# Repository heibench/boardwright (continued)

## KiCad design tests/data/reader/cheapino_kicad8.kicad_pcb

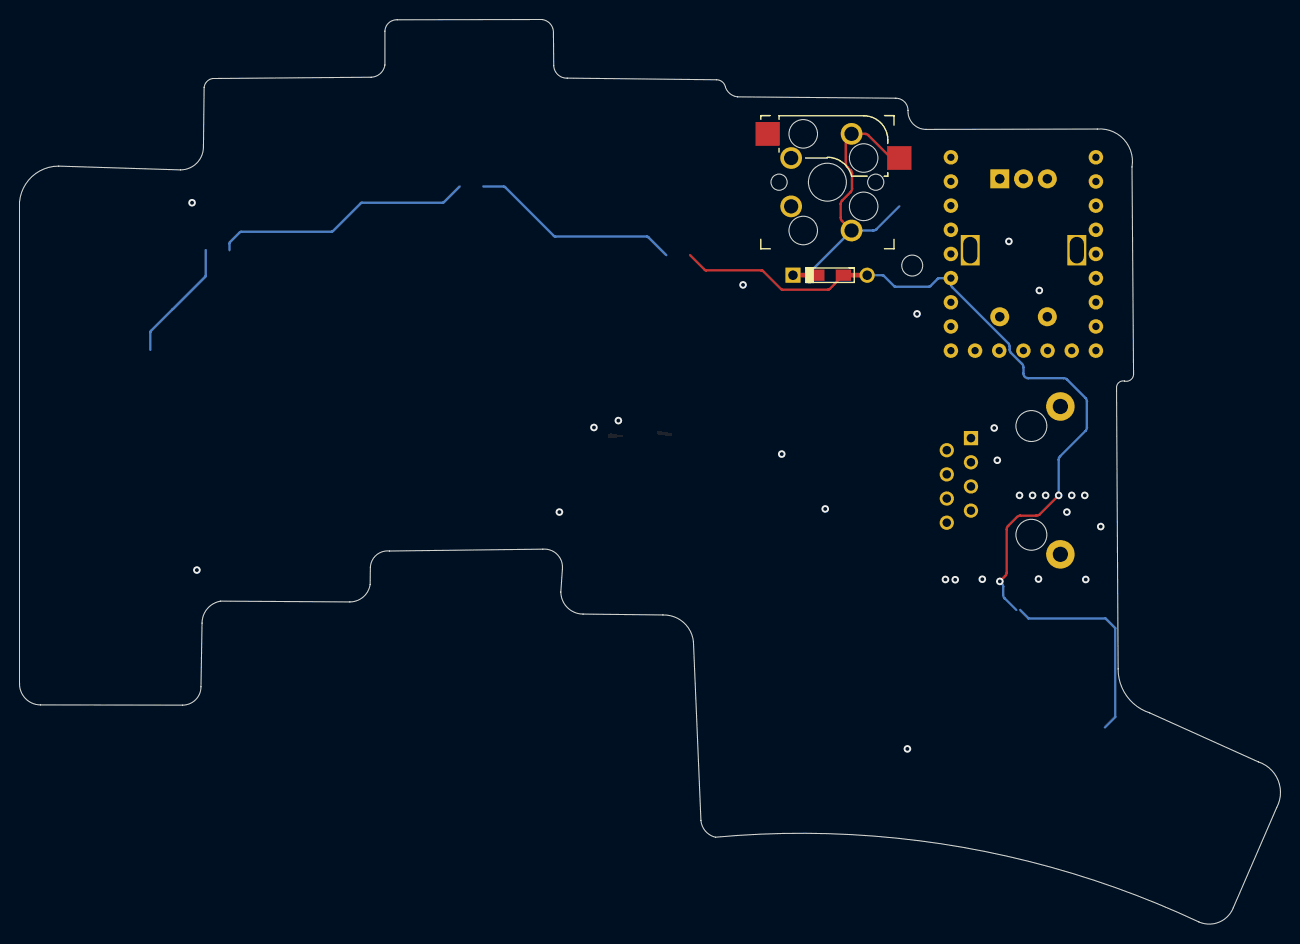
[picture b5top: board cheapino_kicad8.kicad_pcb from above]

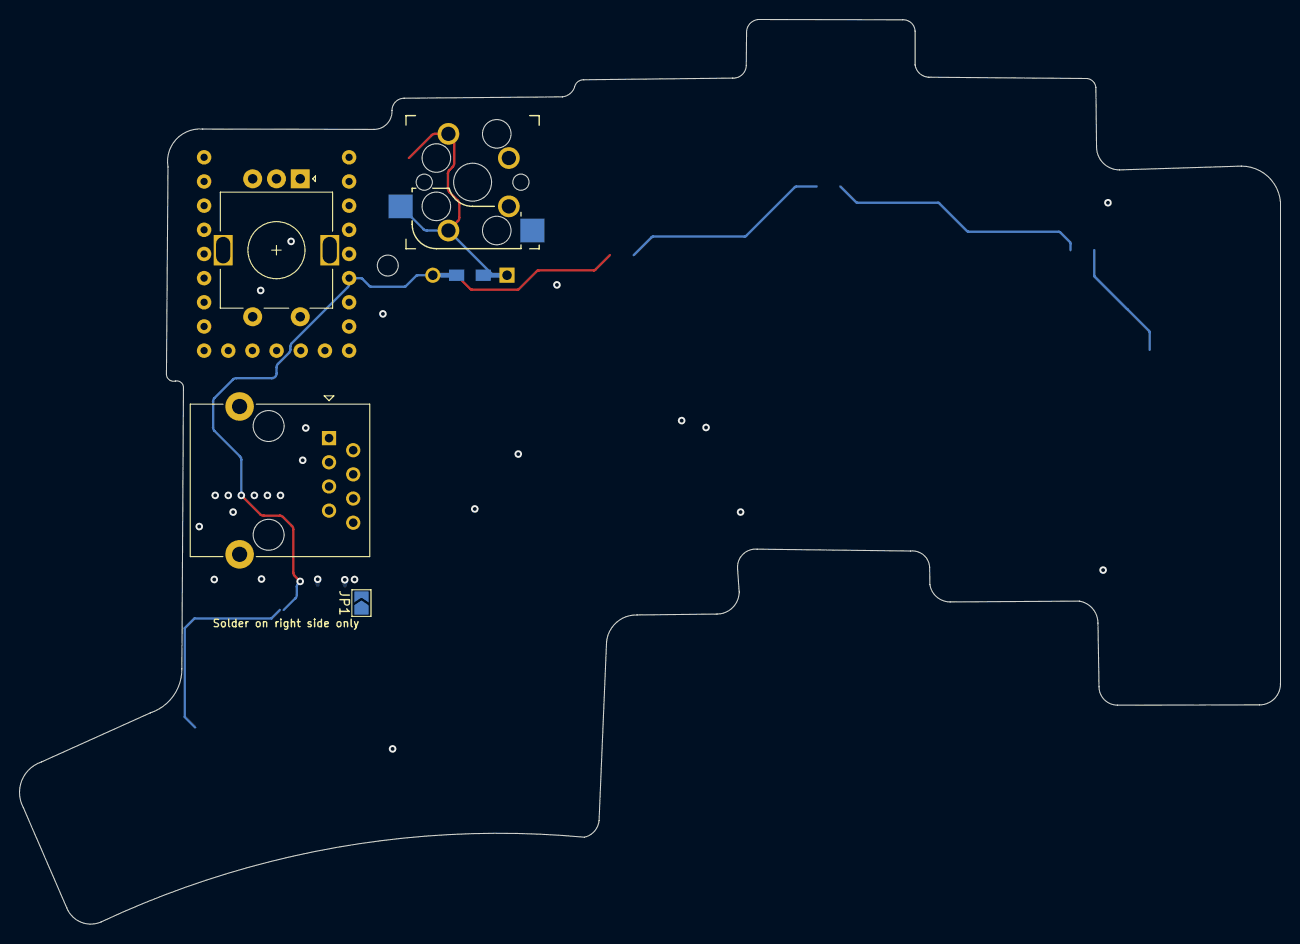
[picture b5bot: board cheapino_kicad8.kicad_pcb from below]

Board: 2 copper layers, 132.5 x 95.1 mm, 6 parts (3 on the bottom side), 12 nets.

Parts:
D1: DIODE; Diode-dual
ENC1: RotaryEncoder_Switch; RotaryEncoder_Alps_EC11E-Switch_Vertical_H20mm
JP1: SolderJumper_2_Open; SolderJumper-2_P1.3mm_Open_TrianglePad1.0x1.5mm
J_2_RIGHT1: RJ45_Shielded; RJ45_Ninigi_GE
K1: SW_Push; Kailh_socket_MX_optional_reversible
U1: RP2040-Zero; MCU_RP2040_Zero_34

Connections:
COL_1: JP1.1 (A), K1.1, U1.14 (GP14)
GND: J_2_RIGHT1.1, J_2_RIGHT1.SH, U1.31 (GND)
unnamed: D1.1 (K), K1.2
ROW_1: D1.2 (A), U1.27 (GP27)
ROW_4: ENC1.C, ENC1.S2, U1.8 (GP8)
R_COL_1: JP1.2 (B), J_2_RIGHT1.8, U1.0 (GP0)
R_COL_2: J_2_RIGHT1.7, U1.1 (GP1)
R_COL_3: J_2_RIGHT1.6, U1.2 (GP2)
R_ROW_1: J_2_RIGHT1.5, U1.3 (GP3)
R_ROW_2: J_2_RIGHT1.4, U1.4 (GP4)
R_ROW_3: J_2_RIGHT1.3, U1.5 (GP5)
R_ROW_4: J_2_RIGHT1.2, U1.6 (GP6)

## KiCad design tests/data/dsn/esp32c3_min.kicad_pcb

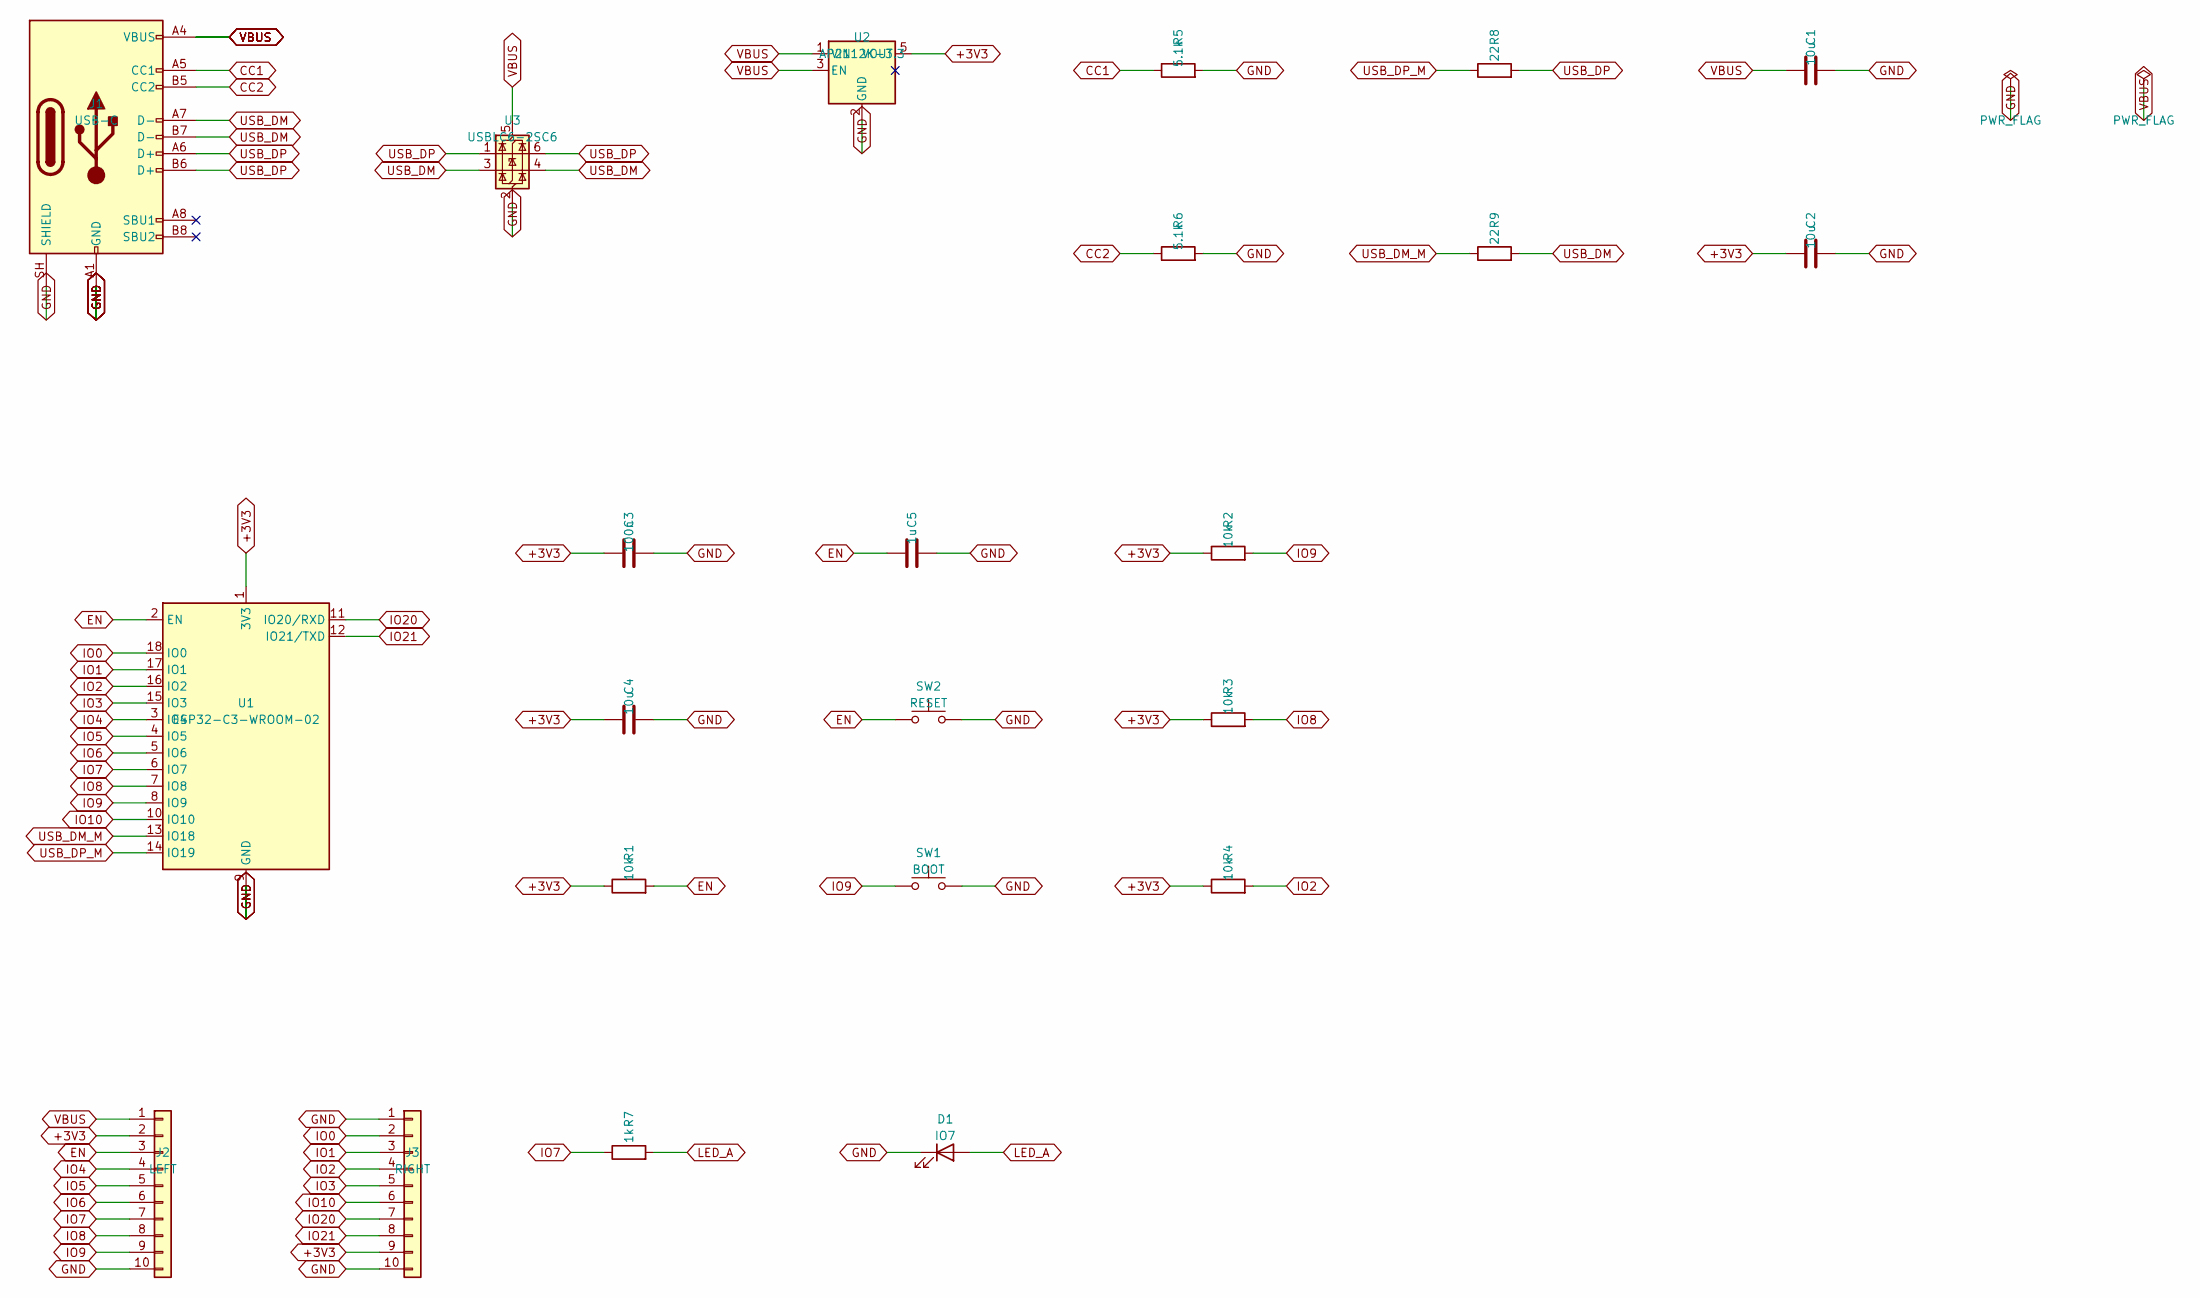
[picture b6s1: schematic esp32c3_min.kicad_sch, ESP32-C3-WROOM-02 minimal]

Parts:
C1, C2, C4: 10u; C_0805_2012Metric
C3: 100n; C_0402_1005Metric
C5: 1u; C_0402_1005Metric
D1: IO7; LED_0603_1608Metric
J1: USB-C; USB_C_Receptacle_GCT_USB4105-xx-A_16P_TopMnt_Horizontal
J2: LEFT; PinHeader_1x10_P2.54mm_Vertical
J3: RIGHT; PinHeader_1x10_P2.54mm_Vertical
R1, R2, R3, R4: 10k; R_0402_1005Metric
R5, R6: 5.1k; R_0402_1005Metric
R7: 1k; R_0402_1005Metric
R8, R9: 22; R_0402_1005Metric
SW1: BOOT; SW_SPST_EVQP0
SW2: RESET; SW_SPST_EVQP0
U1: ESP32-C3-WROOM-02
U2: AP2112K-3.3; SOT-23-5
U3: USBLC6-2SC6; SOT-23-6

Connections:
+3V3: C2.1, C3.1, C4.1, J2.2, J3.9, R1.1, R2.1, R3.1, R4.1, U1.1 (3V3), U2.5 (VOUT)
CC1: J1.A5 (CC1), R5.1
CC2: J1.B5 (CC2), R6.1
EN: C5.1, J2.3, R1.2, SW2.1, U1.2 (EN)
IO0: J3.2, U1.18 (IO0)
IO1: J3.3, U1.17 (IO1)
IO2: J3.4, R4.2, U1.16 (IO2)
IO3: J3.5, U1.15 (IO3)
IO4: J2.4, U1.3 (IO4)
IO5: J2.5, U1.4 (IO5)
IO6: J2.6, U1.5 (IO6)
IO7: J2.7, R7.1, U1.6 (IO7)
IO8: J2.8, R3.2, U1.7 (IO8)
IO9: J2.9, R2.2, SW1.1, U1.8 (IO9)
IO10: J3.6, U1.10 (IO10)
IO20: J3.7, U1.11 (IO20/RXD)
IO21: J3.8, U1.12 (IO21/TXD)
LED_A: D1.2 (A), R7.2
USB_DM: J1.A7 (D-), J1.B7 (D-), R9.2, U3.3 (I/O2), U3.4 (I/O2)
USB_DM_M: R9.1, U1.13 (IO18)
USB_DP: J1.A6 (D+), J1.B6 (D+), R8.2, U3.1 (I/O1), U3.6 (I/O1)
USB_DP_M: R8.1, U1.14 (IO19)

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
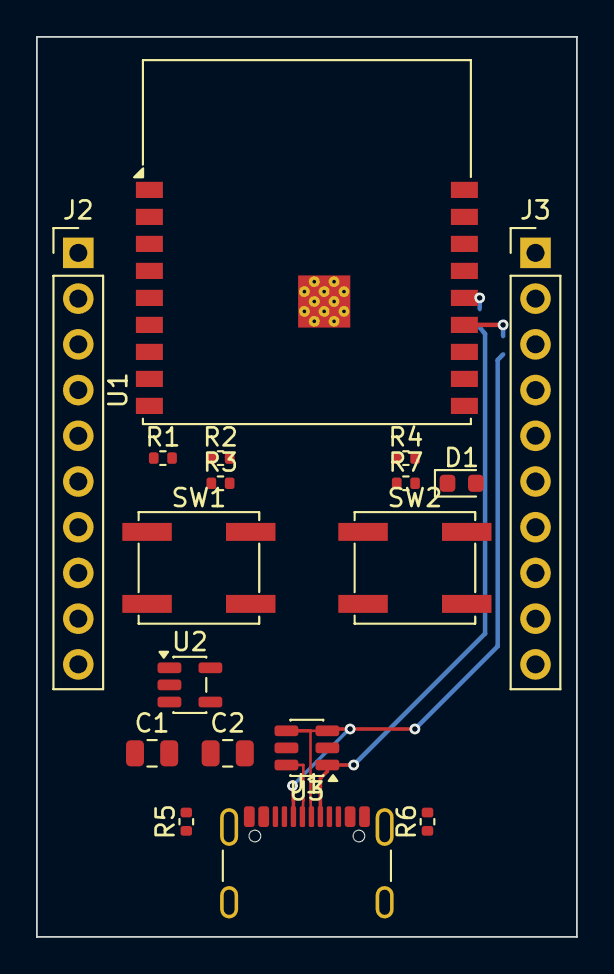
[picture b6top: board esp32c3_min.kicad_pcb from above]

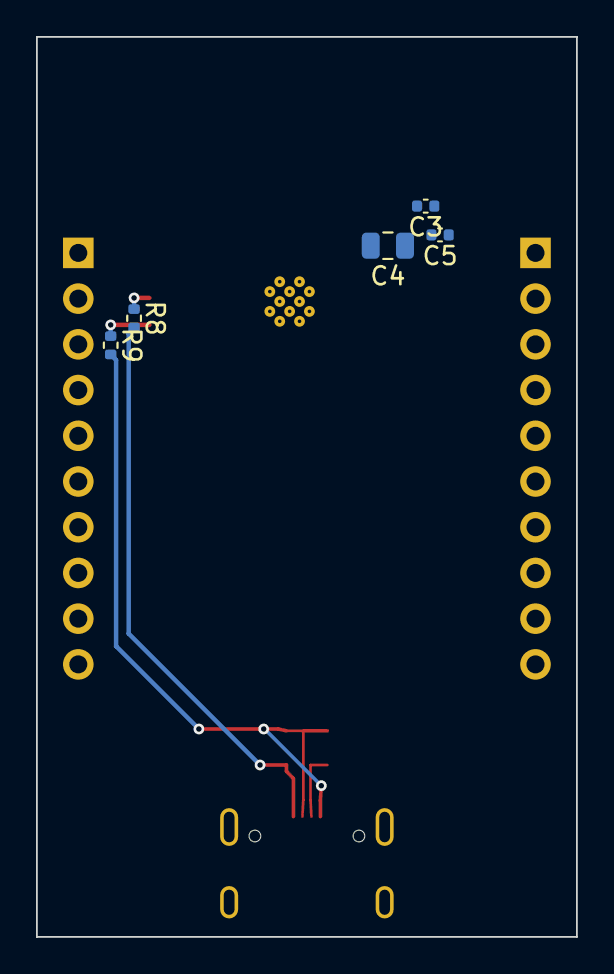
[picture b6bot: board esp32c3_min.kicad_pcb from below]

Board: 2 copper layers, 30.0 x 50.0 mm, 23 parts (5 on the bottom side), 24 nets.

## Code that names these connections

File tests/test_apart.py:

"""REVIEW "apart" and "clear_under": quiet copper kept from noise (#125).
Boards are copies of the examples, edited: one that passes, one that fails
with the named finding, and one with what the check reads removed."""

import re
from types import SimpleNamespace

from conftest import BOARDS
from test_placement_review import _fp

from boardwright.model import Board
from boardwright.review import apart_check, review

BUCK = BOARDS / "tps54202_buck" / "tps54202_buck.kicad_pcb"
STM = BOARDS / "stm32f103_min" / "stm32f103_min.kicad_pcb"
STM4 = BOARDS / "stm32f103_4l" / "stm32f103_4l.kicad_pcb"


def _board(tmp_path, src, edit=None):
    pcb = tmp_path / src.name
    text = src.read_text()
    pcb.write_text(edit(text) if edit else text)
    return Board(pcb)


def _under_boot0(layer):
    """A NOISE track on `layer` right under BOOT0's F.Cu track (file coordinates;
    BOOT0 has no via, so its copper is on F.Cu alone)."""
    seg = (f'\t(segment (start 139.92 95.3) (end 145.68 95.3) (width 0.2) (layer "{layer}") (net "NOISE") '
           f'(uuid "00000000-0000-0000-0000-000000000002"))\n')
    return lambda t: t[:t.rstrip().rfind(")")] + seg + t[t.rstrip().rfind(")"):]


def test_feedback_clear_of_the_switch_node_passes(tmp_path):
    lines, fails = apart_check(_board(tmp_path, BUCK), {"apart": [("FB", ["SW"], 0.9)]})
    assert fails == []
    assert lines == ["apart FB | SW: 1.00 mm (FB to SW, F.Cu) (>= 0.9)"]


def test_feedback_near_the_switch_node_fails(tmp_path):
    fails = apart_check(_board(tmp_path, BUCK), {"apart": [("FB", "SW", 1.2)]})[1]
    assert len(fails) == 1 and re.fullmatch(
        r"FB comes within 1\.00 mm of SW on F\.Cu, near \([\d.]+, [\d.]+\), limit 1\.2", fails[0])


def test_a_quiet_net_with_no_copper_cannot_judge(tmp_path):
    fails = apart_check(_board(tmp_path, BUCK), {"apart": [("NOPE", "SW", 1.2)]})[1]
    assert fails == ["apart NOPE | SW: cannot judge, no copper on NOPE"]


def test_noise_on_the_adjacent_layer_counts(tmp_path):
    fails = apart_check(_board(tmp_path, STM4, _under_boot0("In1.Cu")), {"apart": [("BOOT0", "NOISE", 0.5)]})[1]
    assert len(fails) == 1 and fails[0].startswith("BOOT0 comes within 0.00 mm of NOISE on F.Cu/In1.Cu")


def test_noise_two_layers_down_does_not(tmp_path):
    lines, fails = apart_check(_board(tmp_path, STM4, _under_boot0("In2.Cu")), {"apart": [("BOOT0", "NOISE", 0.5)]})
    assert fails == [] and lines == ["apart BOOT0 | NOISE: no copper on the same or an adjacent layer"]


def test_nothing_under_a_part_passes(tmp_path):
    lines, fails = apart_check(_board(tmp_path, STM), {"clear_under": [("R1", 0.2)]})
    assert fails == [] and lines == ["clear_under R1 (+0.2 mm): clear"]


def test_tracks_under_the_crystal_fail(tmp_path):
    fails = apart_check(_board(tmp_path, STM), {"clear_under": [("Y1", 0.2)]})[1]
    assert fails == ["PA1, PA2, PA4, PC15 run under Y1 (courtyard + 0.2 mm)"]


def test_a_part_with_no_courtyard_cannot_judge(tmp_path):
    strip = lambda blk: re.sub(r'\n\t\t\(fp_(?:line|rect|poly|circle)(?:(?!\n\t\t\().)*?\(layer "F\.CrtYd"\).*?\n\t\t\)', "", blk, flags=re.S)  # noqa: E731
    b = _board(tmp_path, STM, lambda t: _fp(t, "Y1", strip))
    assert apart_check(b, {"clear_under": [("Y1", 0.2)]})[1] == ["clear_under Y1: cannot judge, no courtyard"]


def test_review_runs_both_keys(tmp_path):
    b = _board(tmp_path, BUCK)
    fails = review(b.path, SimpleNamespace(REVIEW={"apart": [("FB", "SW", 1.2)], "clear_under": [("U1", 99)]}))
    assert any(f.startswith("FB comes within 1.00 mm of SW") for f in fails)
    assert any(f.endswith("under U1 (courtyard + 99 mm)") for f in fails)


def test_two_pads_of_one_part_are_left_out(tmp_path):
    """PA1 stripped to its pad: its nearest PA2 copper is PA2's track at 0.25 mm,
    not PA2's pad beside it on U1 at 0.20 mm, which the pinout fixes."""
    from test_loop import _no_tracks

    def edit(t):
        t = _no_tracks("PA1")(t)
        return re.sub(r'\n\t\(via(?:(?!\n\t\().)*?\(net "PA1"\).*?\n\t\)', "", t, flags=re.S)
    lines = apart_check(_board(tmp_path, STM, edit), {"apart": [("PA1", "PA2", 0)]})[0]
    assert lines == ["apart PA1 | PA2: 0.25 mm (PA1 to PA2, F.Cu) (>= 0)"]


def test_ground_under_a_part_is_allowed(tmp_path):
    """A GND track crosses SW1's courtyard; it is not listed."""
    assert apart_check(_board(tmp_path, STM), {"clear_under": [("SW1", 0.3)]})[0] == [
        "clear_under SW1 (+0.3 mm): NRST, PC13, PC14, PC15, VBUS"]


def test_another_parts_pads_under_are_not_tracks(tmp_path):
    """C3 sits on the back under U1: U1's PB12 and PB13 pads are inside its
    courtyard, and are the IC it decouples; only the PB14 track counts."""
    assert apart_check(_board(tmp_path, STM), {"clear_under": [("C3", 0.2)]})[0] == ["clear_under C3 (+0.2 mm): PB14"]

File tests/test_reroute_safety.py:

"""`existing reroute` and `existing apply` change nothing when they cannot finish
(#104, #105, #107). The router here is a stand-in: these failures happen before
or instead of a route, so they need no Freerouting."""

import hashlib
import sys

import pytest

from boardwright import copper, dsn, env
from boardwright.cli import main
from boardwright.errors import EnvironmentFault, Usage


def _hash(p):
    return hashlib.sha256(p.read_bytes()).hexdigest()


@pytest.fixture
def board(ldo_copy):
    return ldo_copy / "ldo_breakout.kicad_pcb"


@pytest.mark.parametrize("router, spec, says", [
    ("pass", "", "freerouting produced no SES"),
    ("import time; time.sleep(30)", "FR_TIMEOUT = 0.5\n", "freerouting did not finish in FR_TIMEOUT = 0.5 s"),
], ids=["no SES", "timeout"])
def test_a_failed_reroute_leaves_the_board_as_it_was(ldo_copy, board, monkeypatch, capsys, router, spec, says):
    """It wrote the ripped-up board and left it there: LED_A's track was gone,
    and a timeout said "nothing was checked or written" (#104)."""
    monkeypatch.setattr(env, "freerouting", lambda: [sys.executable, "-c", router])
    if spec:
        (ldo_copy / "boardwright.py").write_text(spec)
    before = _hash(board)
    assert main(["existing", str(ldo_copy), "reroute", "LED_A"]) == 4
    err = capsys.readouterr().err
    assert says in err and "restored as it was read; nothing changed" in err
    assert _hash(board) == before


def test_an_open_outline_stops_the_export_naming_its_ends(ldo_copy, board, monkeypatch, capsys):
    """A 5 um gap gave a DSN with no boundary, on which Freerouting 2.5.0 throws
    a NullPointerException (#105). Now the export refuses, and reroute leaves the
    board as it was."""
    t = board.read_text()
    a = "(gr_line\n\t\t(start 133.5 95)\n\t\t(end 163.5 95)"
    assert t.count(a) == 1
    board.write_text(t.replace(a, "(gr_line\n\t\t(start 133.5 95)\n\t\t(end 163.495 95)"))
    with pytest.raises(EnvironmentFault, match=r"open ends at \(163\.495, 95\), \(163\.5, 95\)"):
        dsn.export(board, ldo_copy / "x.dsn")
    monkeypatch.setattr(env, "freerouting", lambda: pytest.fail("no route without an outline"))
    before = _hash(board)
    assert main(["existing", str(ldo_copy), "reroute", "LED_A"]) == 4
    assert "does not close within 1 um" in capsys.readouterr().err
    assert _hash(board) == before


@pytest.mark.parametrize("entry", [("LED_A", (10.0, 10.0)), ("LED_A", 10.0), ("LED_A", 1.0, 2.0, 0.6),
                                   (None, 1.0, 2.0), ("LED_A", "1", 2.0), "LED_A"])
def test_a_via_in_another_form_is_a_usage_error(entry):
    with pytest.raises(Usage, match=r"is not \(net, x, y\[, size, drill\]\)"):
        copper.check_vias(type("M", (), {"VIAS": [entry]}))


@pytest.mark.parametrize("entry", [("LED_A", 1.0, 2.0), ("LED_A", 1, 2, 0.6, 0.3), ["LED_A", 1.0, 2.0]])
def test_the_documented_via_forms_pass(entry):
    copper.check_vias(type("M", (), {"VIAS": [entry]}))


def test_apply_refuses_a_bad_via_before_ripping_anything_up(ldo_copy, board, capsys):
    """It ripped up and moved first, then crashed with an IndexError, exit 2 (#107)."""
    (ldo_copy / "boardwright.py").write_text('RIPUP = ["LED_A"]\nVIAS = [("LED_A", (10.0, 10.0))]\n')
    before = _hash(board)
    assert main(["existing", str(ldo_copy), "apply"]) == 64
    assert "VIAS entry ('LED_A', (10.0, 10.0)) is not (net, x, y[, size, drill])" in capsys.readouterr().err
    assert _hash(board) == before


def test_plane_layers_are_the_inner_zone_only_layers_unless_planes_says():
    """#106: reroute ran signals through stm32f103_4l's In1/In2 GND planes."""
    from types import SimpleNamespace

    from conftest import BOARDS

    from boardwright import existing
    from boardwright.model import Board

    four = Board(BOARDS / "stm32f103_4l" / "stm32f103_4l.kicad_pcb")
    two = Board(BOARDS / "ldo_breakout" / "ldo_breakout.kicad_pcb")      # GND pour on both outer layers
    none = SimpleNamespace()
    assert existing.plane_layers(four, none) == ["In1.Cu", "In2.Cu"]
    assert existing.plane_layers(two, none) == []
    assert existing.plane_layers(four, SimpleNamespace(PLANES=["In2.Cu"])) == ["In2.Cu"]
    assert existing.plane_layers(four, SimpleNamespace(PLANES={"In1.Cu": "GND"})) == ["In1.Cu"]
    assert existing.plane_layers(four, SimpleNamespace(PLANES=[])) == []
    with pytest.raises(Usage, match="In3.Cu"):
        existing.plane_layers(four, SimpleNamespace(PLANES=["In3.Cu"]))


def test_reroute_hands_freerouting_the_planes_switched_off(tmp_path, monkeypatch, capsys):
    import shutil

    from conftest import BOARDS

    d = tmp_path / "b"
    shutil.copytree(BOARDS / "stm32f103_4l", d, ignore=shutil.ignore_patterns("out", "boardwright_out", "board.py"))
    seen = tmp_path / "argv"
    monkeypatch.setattr(env, "freerouting",
                        lambda: [sys.executable, "-c", f"import sys; open({str(seen)!r}, 'w').write(repr(sys.argv))"])
    assert main(["existing", str(d), "reroute", "PA1"]) == 4                 # the stand-in writes no SES
    argv = eval(seen.read_text())
    rules = (d / "boardwright_out" / "stm32f103_4l.rules").read_text()
    assert argv[argv.index("-dr") + 1].endswith("stm32f103_4l.rules")
    assert "(layer_rule In1.Cu\n      (active off)" in rules and "(layer_rule In2.Cu\n      (active off)" in rules
    assert "(layer_rule F.Cu\n      (active on)" in rules and "(layer_rule B.Cu\n      (active on)" in rules
    assert "kept off the plane layer(s) In1.Cu, In2.Cu" in capsys.readouterr().out


def test_a_net_the_router_cannot_finish_refuses_the_whole_reroute(ldo_copy, board, monkeypatch, capsys):
    """Its old copper, put back, landed on the other named nets' new routes:
    two shorts with PA0 and PA1 on stm32f103_4l (#106). Now nothing changes."""
    from pathlib import Path

    ses = Path(__file__).parent / "data" / "ses" / "ldo_routed.ses"
    t = ses.read_text()
    i = t.index('      (net "LED_A"')
    j = t.index("\n      (net ", i + 1) if "\n      (net " in t[i + 1:] else t.rindex("\n    )")
    t = t[:i] + t[j + 1:]
    # the session was saved from a routed board, so +3V3's via is marked protect,
    # which reroute leaves out as the board's own; a real router gives a ripped
    # net's via back unprotected, and without it +3V3 is open too (#134)
    k = t.index('(via "Via[0-1]_Pad600_um" 1550681 1079552')
    t = t[:k] + t[k:].replace("\n          (type protect)", "", 1)
    partial = ldo_copy / "partial.ses"
    partial.write_text(t)
    copy = "import shutil, sys; shutil.copy(sys.argv[1], sys.argv[sys.argv.index('-do') + 1])"
    monkeypatch.setattr(env, "freerouting", lambda: [sys.executable, "-c", copy, str(partial)])
    before = _hash(board)
    assert main(["existing", str(ldo_copy), "reroute", "LED_A", "+3V3"]) == 1
    err = capsys.readouterr().err
    assert "refused: the router could not finish ['LED_A']; reroute ['+3V3'] without them" in err
    assert _hash(board) == before


def test_an_outer_pour_with_no_tracks_is_still_routed_on():
    """A two-layer board routed on top with GND poured on the bottom keeps both
    layers: only inner layers are planes by default."""
    from types import SimpleNamespace

    from boardwright import existing

    b = SimpleNamespace(layers=["F.Cu", "B.Cu"], zones=[SimpleNamespace(layers=["B.Cu"], keepout=False)],
                        tracks=[SimpleNamespace(layer="F.Cu")])
    assert existing.plane_layers(b, SimpleNamespace()) == []


@pytest.fixture
def buck(tmp_path):
    import shutil

    from conftest import BOARDS
    dst = tmp_path / "tps54202_buck"
    shutil.copytree(BOARDS / "tps54202_buck", dst, ignore=shutil.ignore_patterns("out", "boardwright_out", "__pycache__"))
    return dst


def test_reroute_refuses_to_replace_wide_tracks(buck, monkeypatch, capsys):
    """The buck's VOUT tracks are 0.5 mm in a 0.4 mm class; the router would
    put them back at 0.4 mm (#137). Nothing runs, nothing changes."""
    monkeypatch.setattr(env, "freerouting", lambda: pytest.fail("the router ran"))
    pcb = buck / "tps54202_buck.kicad_pcb"
    before = _hash(pcb)
    assert main(["existing", str(buck), "reroute", "VOUT"]) == 1
    cap = capsys.readouterr()
    assert "WIDE VOUT 0.5 mm on F.Cu (class 0.4 mm) from (" in cap.out
    assert ("refused: " in cap.err and "on ['VOUT'] are wider than their net class" in cap.err
            and "--force reroutes them anyway" in cap.err)
    assert _hash(pcb) == before


def test_reroute_force_replaces_wide_tracks(buck, monkeypatch, capsys):
    """--force gets past the check to the router (here one that writes no session)."""
    monkeypatch.setattr(env, "freerouting", lambda: [sys.executable, "-c", "pass"])
    assert main(["existing", str(buck), "reroute", "VOUT", "--force"]) == 4
    cap = capsys.readouterr()
    assert "WIDE" not in cap.out and "freerouting produced no SES" in cap.err
